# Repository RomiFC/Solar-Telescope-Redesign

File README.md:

# Solar-Telescope-Redesign

This goal of this project is to redesign and modernize a solar telescope initially created some time before 2013. The telescope receives RF energy from the sun through an x-band feed horn antenna, amplifies and rectifies the signal, then outputs the signal to a voltmeter. More information is available under the [official documentation](/Report/002.35.25.05.20-002-REP-SolarTeleRedesign.pdf).

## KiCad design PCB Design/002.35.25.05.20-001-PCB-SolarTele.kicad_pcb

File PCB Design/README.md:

# Changelog

## Revision B - 7/24/2024

### Added

- Board characteristics to assembly drawing.
- Board dimensioning to assembly drawing.
- Test points at different stages of amplification.
- Layer indicator to top left of assembly drawing.
- L7912C Negative LDO (Will require additional power supply).
- Summing amplifier stage which will subtract a voltage from the output of the ADL5902-EVALZ in attempt to bring the noise floor closer to 0VDC

### Changed

- Stackup changed from 2-layer, 30 mil RO4350b to 2-layer OSHPark specifications.
- Removed SMA connectors that allowed the stages of the PCB to be used independently as that functionality was not significant.
- Removed ADL5902 Power Detector IC and replaced with a footprint to mount the ADL5902-EVALZ directly on top. Oscillations were detected and further testing is not possible within the current time frame.
- L78XX TO-220 replaced with D2PAK.

### Fixed

- Removed front and back mask from linear regulator pads to improve thermal conductance.
- 15V silkscreen text now correctly reads 12V
- Board dimensions and mounting hole patterns are rounded to clean values (5.05" x 1.8").

## Revision A - 6/29/2023

### First revision 🎉🎉🎉

- This directory contains KiCad files for the PCB. The PCB contains a 15V/5V 1A power supply, an ADL5902 power detector, and a dual LM358 non-inverting amplifier. It was designed to allow users to utilize the individual stages on projects outside of this application.

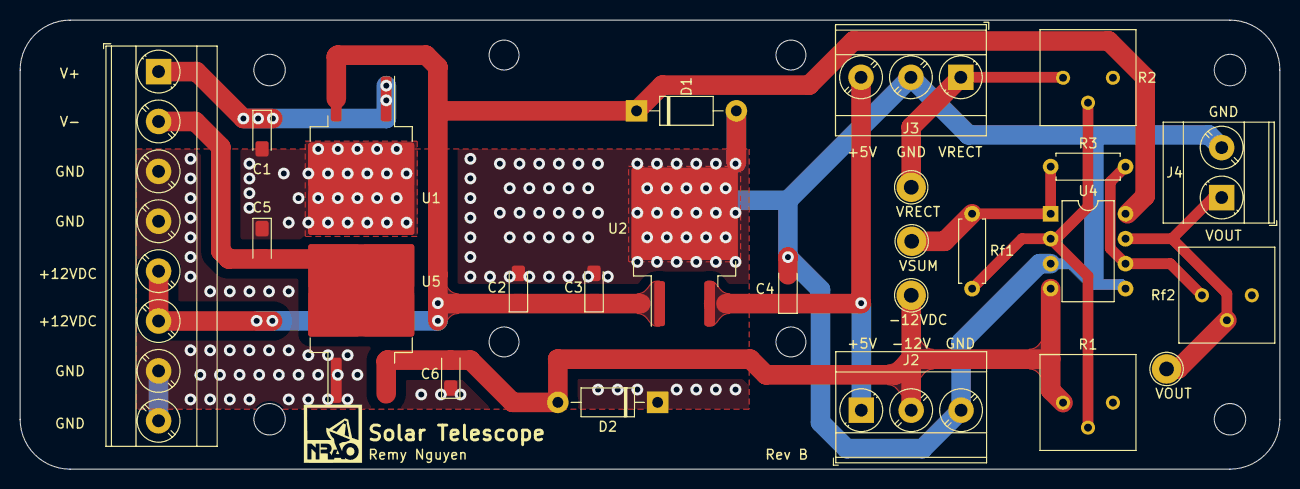
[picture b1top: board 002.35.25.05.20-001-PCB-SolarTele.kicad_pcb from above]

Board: 2 copper layers, 128.3 x 45.7 mm, 26 parts (0 on the bottom side), 11 nets.

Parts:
-12VDC: TestPoint; TestPoint_Loop_D2.54mm_Drill1.5mm_Beaded
C1, C3: 0.33uF; CP_EIA-3216-10_Kemet-I_Pad1.58x1.35mm_HandSolder
C2, C4: 0.1uF; CP_EIA-3216-10_Kemet-I_Pad1.58x1.35mm_HandSolder
C5: 2.2uF; CP_EIA-3216-10_Kemet-I_Pad1.58x1.35mm_HandSolder
C6: 1uF; CP_EIA-3216-10_Kemet-I_Pad1.58x1.35mm_HandSolder
D1, D2: 1N4001; D_DO-41_SOD81_P10.16mm_Horizontal
J1: Screw_Terminal_01x08; TerminalBlock_Phoenix_MKDS-3-8-5.08_1x08_P5.08mm_Horizontal
J2, J3: Screw_Terminal_01x03; TerminalBlock_Phoenix_MKDS-3-3-5.08_1x03_P5.08mm_Horizontal
J4: Screw_Terminal_01x02; TerminalBlock_Phoenix_MKDS-3-2-5.08_1x02_P5.08mm_Horizontal
R1: 50k; Potentiometer_Bourns_3386P_Vertical
R2: 1k; Potentiometer_Bourns_3386P_Vertical
R3: 510; R_Axial_DIN0207_L6.3mm_D2.5mm_P7.62mm_Horizontal
REF: MountingHole_3.2mm_M3_ISO14580
Rf1: 510; R_Axial_DIN0207_L6.3mm_D2.5mm_P7.62mm_Horizontal
Rf2: 10k; Potentiometer_Bourns_3386P_Vertical
U1: L7812; TO-263-2
U2: L7805; TO-263-2
U4: LM358; DIP-8_W7.62mm
U5: L7912; TO-263-2
VOUT: TestPoint; TestPoint_Loop_D2.54mm_Drill1.5mm_Beaded
VRECT: TestPoint; TestPoint_Loop_D2.54mm_Drill1.5mm_Beaded
VSUM: TestPoint; TestPoint_Loop_D2.54mm_Drill1.5mm_Beaded

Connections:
+5VDC: C4.1, J2.1, J3.3, U2.3 (OUT)
+12VDC: C2.1, C3.1, D1.1 (K), J1.5, J1.6, U1.3 (OUT), U2.1 (IN), U4.8 (V+)
-12VDC: -12VDC.1, C6.2, D2.2 (A), J2.2, R1.1, U4.4 (V-), U5.3 (VO)
GND: C1.2, C2.2, C3.2, C4.2, C5.1, C6.1, D1.2 (A), D2.1 (K), J1.3, J1.4, J1.7, J1.8, J2.3, J3.2, J4.2, U1.2 (GND), U2.2 (GND), U4.3 (+), U4.5 (+), U5.1 (GND)
unnamed: R1.2, R2.2, Rf1.1, U4.2 (-)
unnamed: R3.2, Rf2.1, U4.6 (-)
V+: C1.1, J1.1, U1.1 (IN)
V-: C5.2, J1.2, U5.2 (VI)
VOUT: J4.1, Rf2.2, U4.7, VOUT.1
VRECT: J3.1, R2.1, VRECT.1
VSUM: R3.1, Rf1.2, U4.1, VSUM.1

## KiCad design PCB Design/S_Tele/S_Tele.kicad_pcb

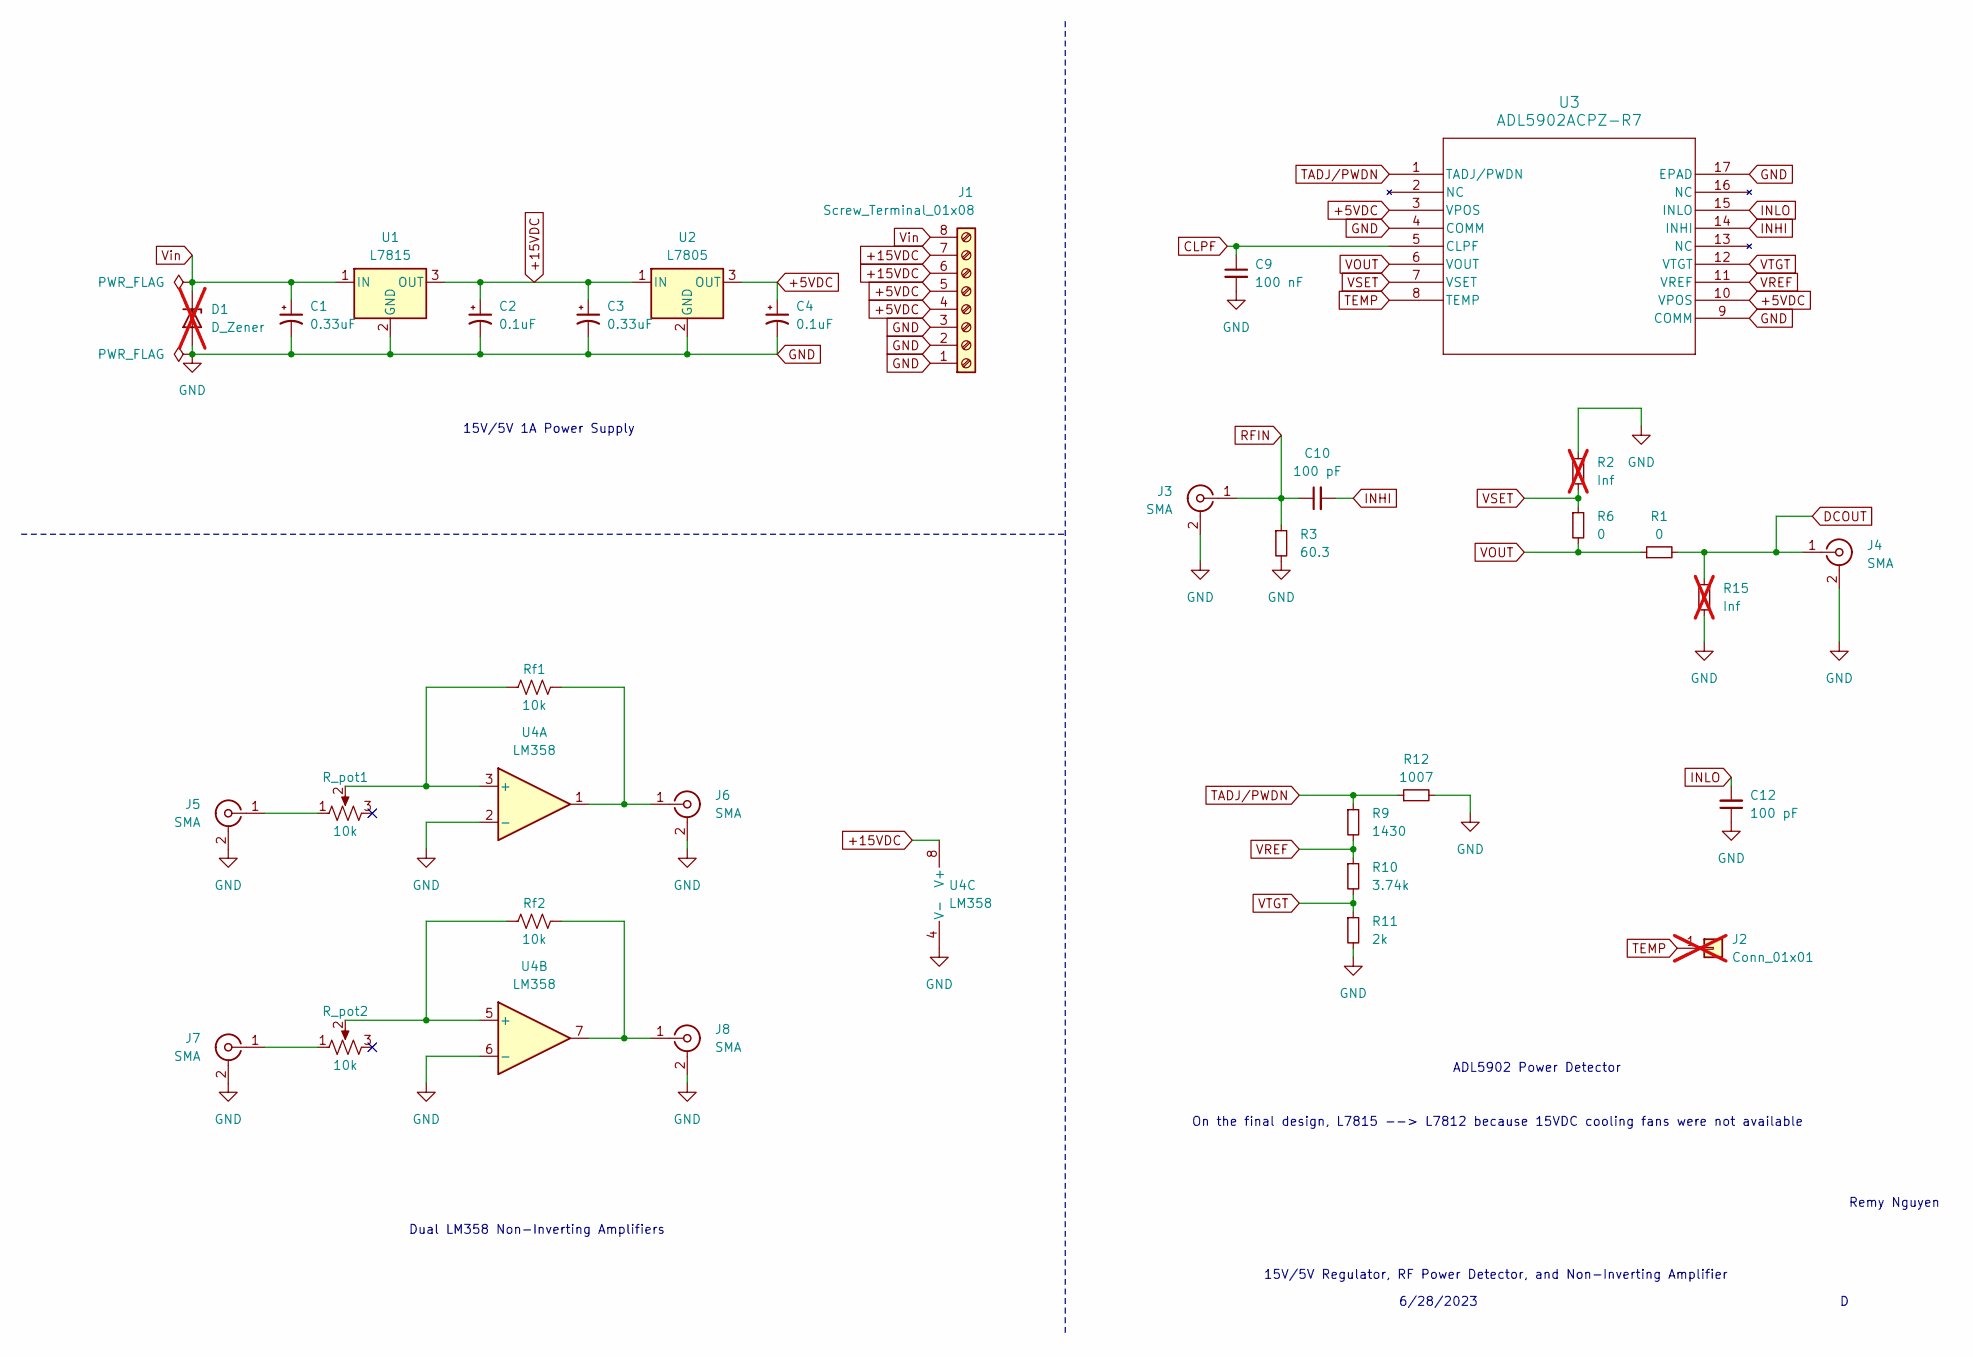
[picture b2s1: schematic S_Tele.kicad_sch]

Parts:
C1, C3: 0.33uF; CP_EIA-2012-12_Kemet-R
C2, C4: 0.1uF; CP_EIA-2012-12_Kemet-R
C9: 100 nF; C_0805_2012Metric
C10, C12: 100 pF; C_1206_3216Metric
D1: D_Zener; D_1206_3216Metric; not fitted
J1: Screw_Terminal_01x08; TerminalBlock_Phoenix_MKDS-3-8-5.08_1x08_P5.08mm_Horizontal
J2: Conn_01x01; PinHeader_1x01_P1.00mm_Vertical; not fitted
J3, J4, J5, J6, J7, J8: SMA; SMA_Molex_73251-1153_EdgeMount_Horizontal
R1, R6: 0; R_1206_3216Metric
R2, R15: Inf; R_1206_3216Metric; not fitted
R3: 60.3; R_0805_2012Metric
R9: 1430; R_1206_3216Metric
R10: 3.74k; R_0805_2012Metric
R11: 2k; R_0805_2012Metric
R12: 1007; R_1206_3216Metric
R_pot1, R_pot2: 10k; Potentiometer_Bourns_3006P_Horizontal
Rf1, Rf2: 10k; R_1206_3216Metric
U1: L7815; TO-220-3_Horizontal_TabDown
U2: L7805; TO-220-3_Horizontal_TabDown
U3: ADL5902ACPZ-R7; CP_16_20_ADI
U4: LM358; DIP-8_W7.62mm

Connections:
+5VDC: C4.1, J1.4, J1.5, U2.3 (OUT), U3.3 (VPOS), U3.10 (VPOS)
+15VDC: C2.1, C3.1, J1.6, J1.7, U1.3 (OUT), U2.1 (IN), U4.8 (V+)
CLPF: C9.1, U3.5 (CLPF)
DCOUT: J4.1 (In), R1.2, R15.1
GND: C1.2, C2.2, C3.2, C4.2, C9.2, C12.1, D1.2 (A), J1.1, J1.2, J1.3, J3.2 (Ext), J4.2 (Ext), J5.2 (Ext), J6.2 (Ext), J7.2 (Ext), J8.2 (Ext), R2.1, R3.2, R11.2, R12.2, R15.2, U1.2 (GND), U2.2 (GND), U3.4 (COMM), U3.9 (COMM), U3.17 (EPAD), U4.2 (-), U4.4 (V-), U4.6 (-)
INHI: C10.2, U3.14 (INHI)
INLO: C12.2, U3.15 (INLO)
unnamed: J5.1 (In), R_pot1.1
unnamed: J6.1 (In), Rf1.2, U4.1
unnamed: J7.1 (In), R_pot2.1
unnamed: J8.1 (In), Rf2.2, U4.7
unnamed: R_pot1.2, Rf1.1, U4.3 (+)
unnamed: R_pot2.2, Rf2.1, U4.5 (+)
RFIN: C10.1, J3.1 (In), R3.1
TADJ/PWDN: R9.1, R12.1, U3.1 (TADJ/PWDN)
TEMP: J2.1, U3.8 (TEMP)
VOUT: R1.1, R6.2, U3.6 (VOUT)
VREF: R9.2, R10.1, U3.11 (VREF)
VSET: R2.2, R6.1, U3.7 (VSET)
VTGT: R10.2, R11.1, U3.12 (VTGT)
Vin: C1.1, D1.1 (K), J1.8, U1.1 (IN)

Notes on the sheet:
6/28/2023
ADL5902 Power Detector
Dual LM358 Non-Inverting Amplifiers
15V/5V 1A Power Supply
Remy Nguyen
On the final design, L7815 --> L7812 because 15VDC cooling fans were not available
15V/5V Regulator, RF Power Detector, and Non-Inverting Amplifier

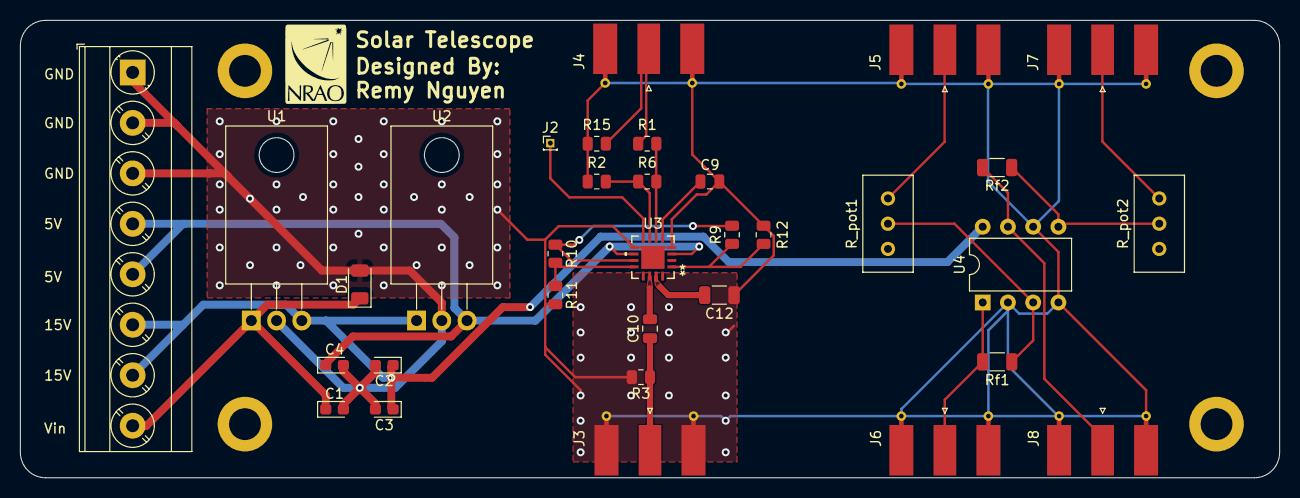
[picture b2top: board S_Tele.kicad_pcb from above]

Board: 2 copper layers, 126.7 x 46.0 mm, 33 parts (0 on the bottom side), 21 nets.

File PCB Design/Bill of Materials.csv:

"#","Reference","Qty","Value","Footprint","DNP"
"1","C1, C3","2","0.33uF","Capacitor_Tantalum_SMD:CP_EIA-2012-12_Kemet-R",""
"2","C2, C4","2","0.1uF","Capacitor_Tantalum_SMD:CP_EIA-2012-12_Kemet-R",""
"3","C9","1","100 nF","Capacitor_SMD:C_0805_2012Metric",""
"4","C10, C12","2","100 pF","Capacitor_SMD:C_1206_3216Metric",""
"5","D1","1","D_Zener","Diode_SMD:D_1206_3216Metric","DNP"
"6","J1","1","Screw_Terminal_01x08","TerminalBlock_Phoenix:TerminalBlock_Phoenix_MKDS-3-8-5.08_1x08_P5.08mm_Horizontal",""
"7","J2","1","Conn_01x01","Connector_PinHeader_1.00mm:PinHeader_1x01_P1.00mm_Vertical","DNP"
"8","J3, J4, J5, J6, J7, J8","6","SMA","Connector_Coaxial:SMA_Molex_73251-1153_EdgeMount_Horizontal",""
"9","R1, R6","2","0","Resistor_SMD:R_1206_3216Metric",""
"10","R2, R15","2","Inf","Resistor_SMD:R_1206_3216Metric","DNP"
"11","R3","1","60.3","Resistor_SMD:R_0805_2012Metric",""
"12","R9","1","1430","Resistor_SMD:R_1206_3216Metric",""
"13","R10","1","3.74k","Resistor_SMD:R_0805_2012Metric",""
"14","R11","1","2k","Resistor_SMD:R_0805_2012Metric",""
"15","R12","1","1007","Resistor_SMD:R_1206_3216Metric",""
"16","R_pot1, R_pot2","2","10k","Potentiometer_THT:Potentiometer_Bourns_3006P_Horizontal",""
"17","Rf1, Rf2","2","10k","Resistor_SMD:R_1206_3216Metric",""
"18","U1","1","L7815","Package_TO_SOT_THT:TO-220-3_Horizontal_TabDown",""
"19","U2","1","L7805","Package_TO_SOT_THT:TO-220-3_Horizontal_TabDown",""
"20","U3","1","ADL5902ACPZ-R7","imports:CP_16_20_ADI",""
"21","U4","1","LM358","Package_DIP:DIP-8_W7.62mm",""

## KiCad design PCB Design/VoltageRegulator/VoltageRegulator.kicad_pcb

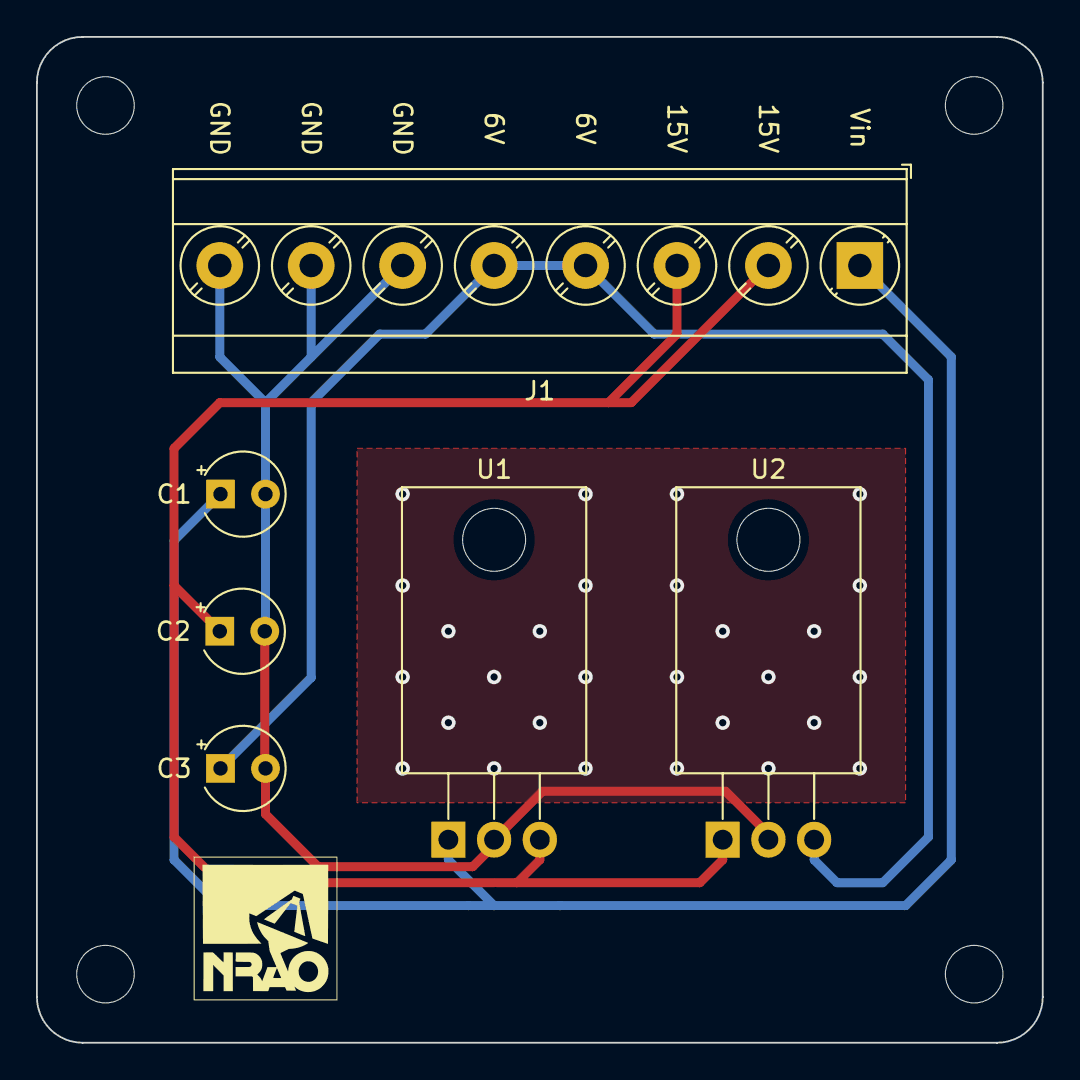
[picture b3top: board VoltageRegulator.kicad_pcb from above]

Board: 2 copper layers, 55.9 x 55.9 mm, 6 parts (0 on the bottom side), 4 nets.

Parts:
C1, C2: 0.33uF; CP_Radial_Tantal_D4.5mm_P2.50mm
C3: 0.1uF; CP_Radial_Tantal_D4.5mm_P2.50mm
J1: Screw_Terminal_01x08; TerminalBlock_Phoenix_MKDS-3-8-5.08_1x08_P5.08mm_Horizontal
U1: LM7815_TO220; TO-220-3_Horizontal_TabDown
U2: LM7806_TO220; TO-220-3_Horizontal_TabDown

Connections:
+6VDC: C3.1, J1.4, J1.5, U2.3 (VO)
+15VDC: C2.1, J1.2, J1.3, U1.3 (VO), U2.1 (VI)
GND: C1.2, C2.2, C3.2, J1.6, J1.7, J1.8, U1.2 (GND), U2.2 (GND)
Vin: C1.1, J1.1, U1.1 (VI)

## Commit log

2023-06-16 New Directory
2023-06-21 PCB completed, new report format
2023-06-23 Continued drafting report
2023-06-26 Continued work on report
2023-06-26 Schematic Rev C
2023-06-27 Schematic Revision C - AD8317
2023-06-27 Schematic Revision D Draft, Datasheets added
2023-06-27 Schematic Rev C complete, ADL5902 pins reassigned; ERC pass
2023-06-27 README files added
2023-06-29 New circuit diagram with current draw
2023-06-29 INLO fixed; INLO is unused differential input, not RFGND
2023-06-29 Footprints assigned, LM7815 --> L7815
2023-06-29 PCB Rev D drafted, DRC pass
2023-06-29 LM358 I/O swapped
2023-06-30 More LNAs added to figure 1
2023-06-30 RF TXline width fixed, GCPW --> CPW
2023-06-30 RF block diagram updated
2023-06-30 Added ADL5902 and fan to power diagram
2023-07-03 Reformatted sections; Bibtex --> Biblatex; new command \nraocite (formatting)
2023-07-07 Bill of materials added
2023-07-10 CPW --> GCPW for RO4350B & silkscreen added
2023-07-10 Removed kicad backups to decrease repo size
2023-07-10 10 mil RO4350B --> 30 mil, RF traces adjusted
2023-07-11 chktek warnings suppressed
2023-07-12 Revert "Merge conflict resolved": KiCad project corrupted
    This reverts commit 708bf57b2537bb9e720d308913f0671883acc423, reversing
    changes made to 03e59d059433c095b682b83f3c3dbb520ea51bac.
2023-07-17 Colored figures and added rf gain block
2023-07-19 Added output scaling circuit to report
2023-07-19 Removed NI Multisim directory
2023-07-20 Reverted output scaling circuit
2023-07-26 Added document numbers
2023-07-28 Added new tansens figure
2023-07-31 Started tansens report
2023-07-31 New report section: Tuning System Gain
2023-08-01 Report edits
2023-08-01 Fixed footprint assignments in schematic
2023-08-01 Moved sections and added citation hyperlinks
2023-08-01 New header format
2023-08-02 Filled header
2023-08-02 Added filter s-parameters
2023-08-04 New spectrum analyzer traces added
2023-08-04 Component S-parameters added to report for reference (temporary)
2023-08-11 Datalogging updated, final experiment traces added
2023-08-11 Final trace and architecture added to report, removed indentations and hbox warnings
2023-08-11 Sch. comment: op-amp topology is incorrect
2023-08-11 Added report change record
2023-08-14 TS measurements for rf-dfs board
2023-08-14 Fixed MATLAB file names
2023-08-14 RF-DFS measurement added to TS report
2023-08-14 REP: Revised calculations for better flow
2023-08-15 Reports complete, sent for review
2023-08-15 Updated .gitignore
2023-08-15 Housekeeping
2023-08-15 Fixed reference hyperlinks
2023-08-15 Changed font to Gill Sans MT and title page pt sizes
2023-08-15 Fixed hyperlink colors
2023-08-16 Edits and review from Tess
2024-01-22 Fixed SMA pad thickness
2024-08-02 PCB updated to Revision B, see changelog for details
2024-09-23 Housekeeping
    - Updated schematic with higher value resistors to prevent backcurrent.
    - Updated schematic with warning on low R2 value causing backcurrent.
    - Removed KiCad/LaTeX auxiliary files and .gitignore'd them.
